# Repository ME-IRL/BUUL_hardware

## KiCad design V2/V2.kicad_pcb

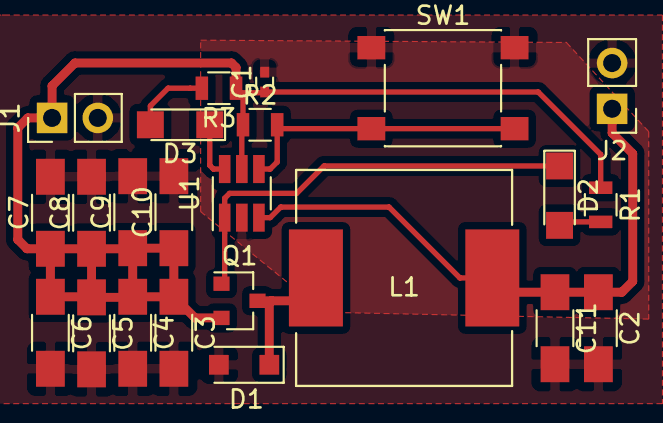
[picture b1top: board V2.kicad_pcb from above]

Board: 2 copper layers, 23 parts (0 on the bottom side), 9 nets.

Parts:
C1: 4.7uF; C_0402
C2, C11: 22uF; C_1206_HandSoldering
C3, C4, C5, C6, C7, C8, C9, C10: 10uF; C_1206_HandSoldering
D1: D; D_SOD-123F
D2, D3: LED; LED_1206
J1, J2: Conn_01x02; Pin_Header_Straight_1x02_Pitch2.54mm
L1: 10uH; WE
Q1: Q_PMOS_GSD; SOT-23
R1, R3: 470; R_0805
R2: 10k; R_0805
SW1: SW_Push; SW_SPST_PTS645
U1: ATtiny10-TS; SOT-23-6_Handsoldering

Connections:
BTN: R2.2, SW1.2, U1.4
GND: C1.2, C2.2, C3.2, C4.2, C5.2, C6.2, C7.2, C8.2, C9.2, C10.2, C11.2, D1.2, J1.2, J2.2, SW1.1, U1.2
GP: D3.1, U1.6
unnamed: D1.1, L1.1, Q1.3
unnamed: D2.2, R1.2
unnamed: D3.2, R3.2
PWM: D2.1, Q1.1, U1.1
V_IN: C1.1, C3.1, C4.1, C5.1, C6.1, C7.1, C8.1, C9.1, C10.1, J1.1, Q1.2, R1.1, R2.1, R3.1, U1.5
V_OUT: C2.1, C11.1, J2.1, L1.2, U1.3

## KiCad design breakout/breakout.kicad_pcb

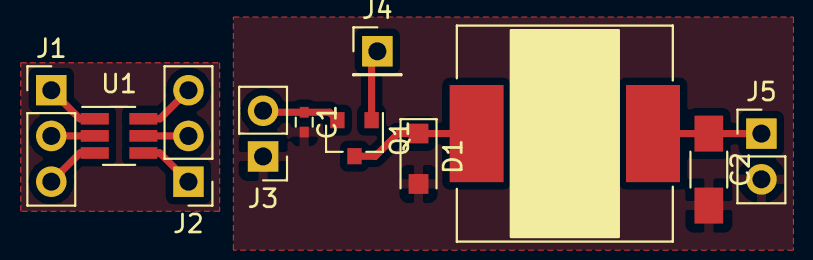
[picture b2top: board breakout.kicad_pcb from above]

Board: 2 copper layers, 11 parts (0 on the bottom side), 11 nets.

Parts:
C1: 4.7uF; C_0402
C2: 22uF; C_1206_HandSoldering
D1: D; D_SOD-123F
J1, J2: Conn_01x03; Pin_Header_Straight_1x03_Pitch2.54mm
J3, J5: Conn_01x02; Pin_Header_Straight_1x02_Pitch2.54mm
J4: Conn_01x01; Pin_Header_Straight_1x01_Pitch2.54mm
L1: 10uH; WE
Q1: Q_PMOS_GSD; SOT-23
U1: ATtiny10-TS; SOT-23-6_Handsoldering

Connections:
GND: C1.2, C2.2, D1.2, J3.1, J5.2
unnamed: C1.1, J3.2, Q1.2
unnamed: C2.1, J5.1, L1.2
unnamed: D1.1, L1.1, Q1.3
unnamed: J1.1, U1.1
unnamed: J1.2, U1.2
unnamed: J1.3, U1.3
unnamed: J2.1, U1.4
unnamed: J2.2, U1.5
unnamed: J2.3, U1.6
unnamed: J4.1, Q1.1

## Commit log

2019-02-14 Breakout board for attiny and buck converter
2019-02-14 Added 3D parts
    Modified base for spring contacts
    Shortened case
